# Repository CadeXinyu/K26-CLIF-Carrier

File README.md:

# K26 Closed-Loop Intan Front End — carrier board, Rev A

Carrier board for the AMD Kria K26 SOM: PCIe x4 edge connector, QSFP28 cage, FMC HPC connector,
four Intan RHD headstage ports, Gigabit Ethernet, USB, SD card and a USB JTAG/UART bridge.

## How to open the design

The easiest way to look at the board is the **KiCad** copy or the **layer PDFs** below.
The original design was made in **EasyEDA Pro** (Chinese name: 嘉立创EDA专业版), version 4.1.97.

### EasyEDA Pro (original, schematic + PCB)

File: **`design/easyeda/K26_CLIF_RevA.epro2`**

- The file was made with the 4.1 release line of the editor. Use version 4.1.97 or newer.
- Web editor with version 4.1: <https://pro.lceda.cn/editor> (the China site; it needs a free account on that site, and the interface language can be set to English).
- Desktop version: <https://lceda.cn/page/download>.
- Open it with **File → Import → EasyEDA (Professional)** and select the `.epro2` file.
- The international site <https://pro.easyeda.com/editor> runs version 3.2 at the time of writing. Importing this file there has not been tested and may fail.

This file is the reference. It contains the schematic (12 pages), the 6-layer PCB, the footprints and the design rules.

### KiCad (converted copy, PCB only)

File: **`design/kicad/K26_CLIF_RevA.kicad_pro`** (open with KiCad 10 or newer)

- It contains the PCB: all six copper layers, tracks, vias, copper pours, silkscreen and the board outline.
- It does not contain the schematic.
- The complete EasyEDA design rules are not carried over. KiCad DRC results need review against the original rules; successful import does not establish manufacturing compliance. Use this copy for viewing and measuring.
- Do not press "Fill all zones" (key B) before migrating and checking the rules. The saved copper has been checked against the original EasyEDA fill; KiCad would refill it differently.
- The 2026-11-17 checked export restores conversion omissions in cage-ground nets, embedded thermal vias, short segments and saved copper. See [conversion details](design/kicad/README.md).

### No software

| What | Where |
|---|---|
| Every layer as PDF, one file per layer | [`docs/layers/`](docs/layers/) |
| All layers in one PDF (12 pages) | [`docs/K26_CLIF_RevA_all_layers.pdf`](docs/K26_CLIF_RevA_all_layers.pdf) |
| Schematic pages as pictures | [`schematic/`](schematic/) |
| Board pictures | [`docs/`](docs/) |
| Gerber files (open with any Gerber viewer) | [`fabrication/K26_CLIF_RevA_Gerber.zip`](fabrication/K26_CLIF_RevA_Gerber.zip) |

The layer PDFs are drawn from the Gerber files, so they show exactly what is sent to the board house.
Pages: L1 top copper, L2 ground, L3 signal, L4 power, L5 ground, L6 bottom copper, top and bottom silkscreen,
top and bottom solder mask openings, top and bottom paste. The bottom-side layers are drawn as seen from the top (not mirrored).

## Routing and power pours

The three signal layers are drawn with the copper pours removed, so only tracks, pads and vias remain.
The power layer is drawn with its rail and ground pours, one colour per net.
A vector PDF of each picture is in [`docs/routing_e/`](docs/routing_e/).
The complete layers as manufactured are in [`docs/layers/`](docs/layers/).

**L1 Top (signal), pours removed**

**L3 (inner signal), pours removed**

**L6 Bottom (signal), pours removed**, seen from the top side, not mirrored

**L4 (power), rail pours and ground pours shown.** The board-wide 3.3 V pour is hidden: 3.3 V fills all the light grey area
that is not taken by another pour. The green areas are ground: the reference under the QSFP pairs and under the PCIe pairs that run on L3 (black lines).

## Stack-up

Six layers, JLCPCB stack-up **JLC06161H-3313**, ordered as 1.6 mm (finished about 1.54 mm).

| Layer | Use | Copper |
|---|---|---|
| L1 Top | Signals and components | 1 oz |
| L2 | Ground plane | 0.5 oz |
| L3 | Inner signals | 0.5 oz |
| L4 | Power planes (12 V, 5 V, 3.3 V, 1.8 V) with ground fill | 0.5 oz |
| L5 | Ground plane | 0.5 oz |
| L6 Bottom | Signals and decoupling parts | 1 oz |

Dielectric between layers: L1–L2 prepreg 3313, 0.0994 mm; L2–L3 core, 0.55 mm; L3–L4 prepreg 2116,
0.1088 mm; L4–L5 core, 0.55 mm; L5–L6 prepreg 3313, 0.0994 mm.

L3 is much closer to L4 than to L2, so the L3 tracks use L4 as their reference plane.

## Fabrication settings used for the JLCPCB quote

- 6 layers, 1.6 mm, stack-up JLC06161H-3313
- Surface finish ENIG, 1 U"
- Vias epoxy filled and capped
- Gold fingers with 30° bevel (PCIe edge)
- Minimum track and gap 0.09 mm
- Assembly on both sides

## Folder contents

| Folder | Contents |
|---|---|
| `design/easyeda/` | EasyEDA Pro project file (original) |
| `design/kicad/` | KiCad 10 copy of the PCB |
| `fabrication/` | Gerber and drill files, BOM and pick-and-place files in JLCPCB format, polarity table, assembly drawings |
| `schematic/` | The 12 schematic pages as PNG |
| `docs/` | Layer PDFs, routing pictures without pours, board renders and the stack-up drawing |

## Notes

- The `.epro2` file is the reference. The Gerber, BOM and pick-and-place files were exported from it.
- The two SOM connectors, the FMC connector and the Intan connectors are not in the assembly BOM.
  They are fitted by hand.
- The board has not been built or tested yet.

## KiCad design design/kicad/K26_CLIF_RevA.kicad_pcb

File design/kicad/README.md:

# KiCad PCB 导出说明

本目录提供与 `../easyeda/K26_CLIF_RevA.epro2` 同版的 KiCad 10 PCB 文件与最小项目文件。源 EDA 保存时间为 2026-11-17 01:33:18，SHA256：

`f1121fc5e281b10cd991b39010013871bc10f00e706a88f5d16b4b076a84ac8c`

- [PCB文件](K26_CLIF_RevA.kicad_pcb)
- [最小项目文件](K26_CLIF_RevA.kicad_pro)
转换核验摘要见 [conversion_validation.json](conversion_validation.json)。先前转换文件已另行备份。

以同版既有 KiCad 转换件为基础，核对后只校正转换丢失：恢复10个QSFP笼地焊盘的GND网名、13段0.00027–0.0023mm极短走线、12个DC/DC封装内热过孔，并将46个铜区的已保存填充恢复为原EDA的POURED实铜轮廓。另以0.1µm容差保拓扑简化已保存铜面轮廓，2355个孔洞轮廓计数保留，使文件从98.2MB降至33.7MB。没有修改原EDA，也没有调用KiCad重新铺铜。原转换件按原字节备份。

重新打开文件后验证：323个命名元件（另66个独立焊盘包装为无名封装），2240个焊盘，6898段直线、19段圆弧、1586个过孔；位置/角度、焊盘网名/尺寸/钻孔及走线几何均对应源。坐标整体平移(+50,+70)mm，板内相对位置不变；焊盘最大坐标差0.373µm，走线/圆弧/过孔按1µm容差核对。30组网络/铜层的保存实铜联合面积最大相对差约0.00330%，2µm容差外未发现面积差。

这是 **PCB-only** 导出；没有配套KiCad原理图，规则、板厂叠层参数、3D模型及完整文档未全部迁移或签核。当前保存的铜面已核对；若在KiCad中重新铺铜，应先核对并迁移设计规则。源设计中已报告的问题也被忠实保留，不能以文件成功打开替代制造检查。

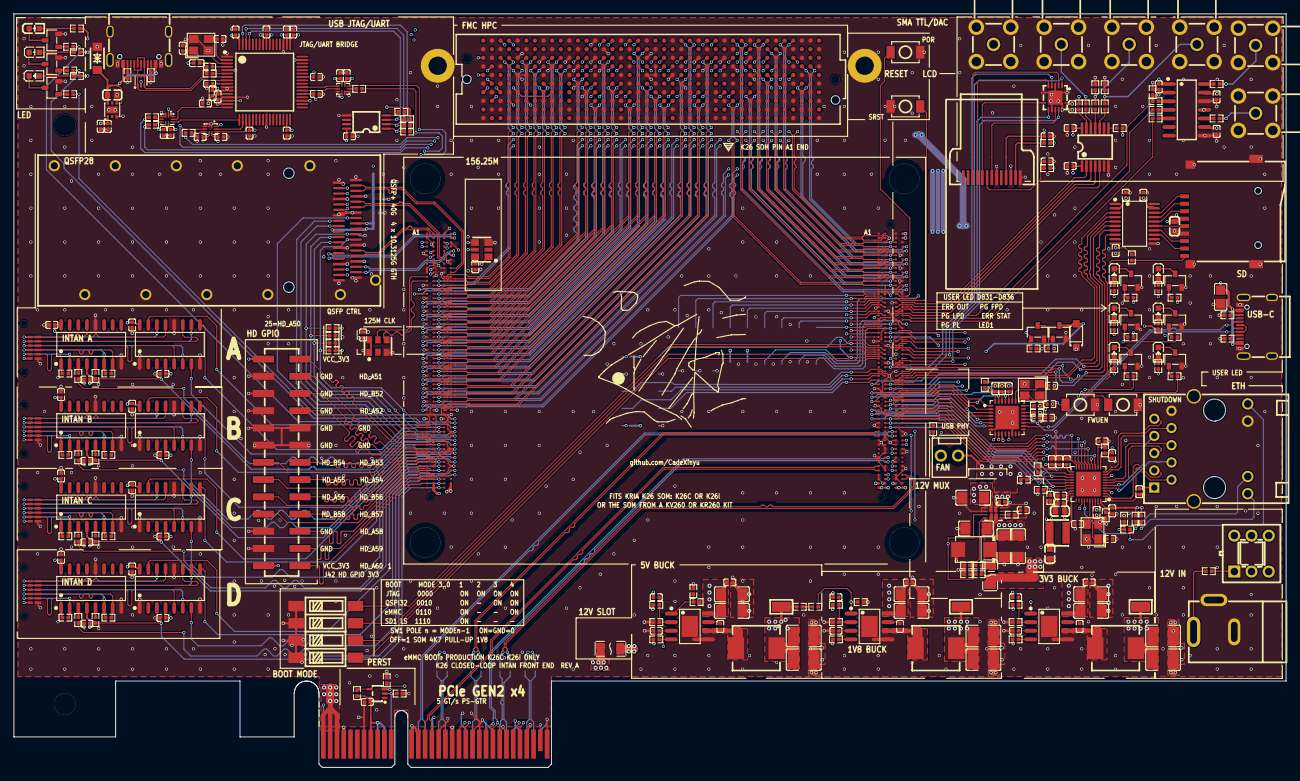
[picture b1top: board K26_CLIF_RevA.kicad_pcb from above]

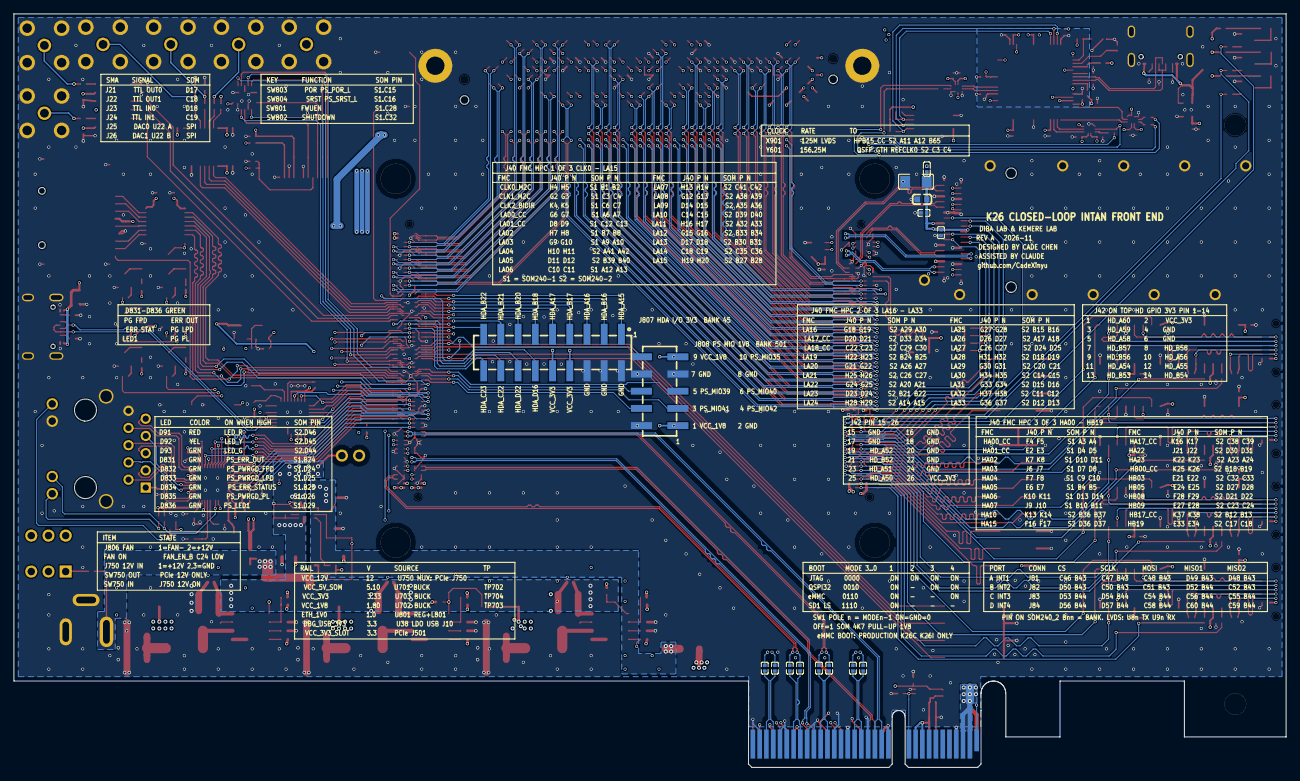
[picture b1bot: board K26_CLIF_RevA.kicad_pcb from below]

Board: 6 copper layers, 187.7 x 111.2 mm, 319 parts (15 on the bottom side), 462 nets.

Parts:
C21, C22, C23, C24, C150, C154, C156, C159, C161, C162, C163, C164, C165, C166, C167, C168, C169, C170, C171, C172, C173, C174, C175, C176, C177, C178, C502, C503, C504, C505, C506, C507, C508, C509, C513, C601, C610, C612, C712, C713, C716, C717, C722, C723, C726, C727, C732, C733, C736, C737, C752, C801, C802, C803, C806, C807, C808, C809, C810, C811, C812, C821, C822, C823, C831, C832, C841, C842, C851, C852, C853, C861, C862, C863, C864, C865, C866, C867, C881, C882, C891, C892, C893, C901, C902, C903, C904, C905, C906, C907, C908, C909, C910, C911, C912, C913: C0402
C155, C611, C804, C805, C883: C0603
C613, C700, C701, C710, C711, C720, C721, C730, C731, C750, C751: C1206
C714, C715, C724, C725, C734, C735: C1210
C868: C0805
D26: SOD-123FL_L2.8-W1.8-LS3.7-BI
D91: LED-SMD_L1.6-W0.8-R-RD
D92: LED0603-R-RD
D93, D831, D832, D833, D834, D835, D836: LED0603-RD
D750: SMB_L4.6-W3.6-LS5.3-RD
D841: SOD-123F_L2.7-W1.6-LS3.8-RD
F750, F751: F1206
FB4, FB5, FB601: L0402
J10, J803: TYPE-C-SMD_SBC-160S1A-20-S412
J21, J22, J23, J24, J25, J26: SMA-TH_KH-SMA-KWE11
J40: CONN-SMD_400P-P1.27-R10-C40
J42: HDR-SMD_26P-P2.54-V-M-R2-C13-LS7.5
J501: J501 — PCIe x4 edge
J602: CONN-SMD_QSFP2849003-00N011
J750: DC-IN-TH_PJ-002AH
J801: RJ45-TH_HR911130A
J805: TF-SMD_TF-01A
J806: CONN-TH_2P-X2510WV-02-N0SN
J807: HDR-SMD_18P-P2.54-V-M-R2-C9-S7.50-1
J808: HDR-SMD_10P-P2.54-V-M-R2-C5-LS7.5
JP701: R0402
K26: K26 — Kria K26 • 180°
L701, L702, L703: IND-SMD_L7.0-W6.6
L801: IND-SMD_L3.0-W3.0
LCD1: OLED-SMD_ST7735S
Q91, Q92, Q93, Q831, Q832, Q833, Q834, Q835, Q836, Q841, Q842: SOT-23-3_L2.9-W1.3-P1.90-LS2.4-BR
R21, R22, R23, R24, R25, R26, R27, R31, R32, R33, R34, R35, R36, R91, R92, R93, R94, R95, R96, R102, R106, R107, R108, R110, R121, R122, R123, R124, R513, R514, R515, R601, R602, R603, R604, R710, R711, R712, R713, R714, R720, R721, R722, R730, R731, R732, R740, R741, R750, R751, R752, R753, R754, R755, R801, R802, R803, R804, R805, R806, R808, R809, R810, R811, R812, R813, R814, R821, R822, R823, R824, R831, R832, R833, R834, R841, R842, R843, R844, R851, R852, R861, R862, R863, R865, R866, R891, R901, R902, R931, R932, R933, R934, R935, R936, R941, R942, R943, R944, R945, R946, R951, R952, R954, R955: R0402
SOM240_1: SOM240_1 — Samtec ADM6 4×60
SOM240_2: SOM240_2 — Samtec ADM6 4×60
SW1: SW-SMD_DSIC04LSGET
SW750: SW-TH_6P-L8.5-W8.5-P2.50-S5.30_PB-22E86
SW801, SW802, SW803, SW804: SW-SMD_L3.9-W3.0-P4.45
TP702, TP703, TP704: SMD_RH-5015
U21: TSSOP-14_L5.0-W4.4-P0.65-LS6.4-BL
U22: SOIC-14_L8.7-W3.9-P1.27-LS6.0-BL
U38: WDFN-6_L2.0-W2.0-P0.65-BL-EP-1
U39: TSSOP-8_L4.4-W3.0-P0.65-LS6.4-BL
U40: LQFP-64_L10.0-W10.0-P0.50-LS12.0-TL
U42, U43, U45: WQFN-10_L1.8-W1.4-P0.40-BL
U60: SOT-563_L1.6-W1.2-P0.50-LS1.6-BL
U81, U82, U83, U84, U91, U92, U93, U94: SOP-16_L10.0-W3.9-P1.27-LS6.0-BL
U511: SC-70-5_L2.1-W1.3-P0.65-LS2.1-BR
U701, U702, U703: SOIC-8_L4.9-W3.9-P1.27-LS6.0-BL-EP
U750: VQFN-HR-12_L2.5-W2.0-P0.50-BL
U801: WQFN-40_L5.0-W5.0-P0.4-BL-EP
U802: QFN-32_L5.0-W5.0-P0.50-BL-EP3.4
U806: TSSOP-20_L6.5-W4.4-P0.65-LS6.4-BL
U807: VQFN-14_L3.5-W3.5-P0.50-BL-EP
X901: OSC-SMD_6P-L3.2-W2.5-BL_SG3225EAN
Y7, Y801, Y802: CRYSTAL-SMD_4P-L3.2-W2.5-BL
Y601: OSC-SMD_6P-L3.2-W2.5-BL

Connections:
BST_1V8: C723.2, U702.7
BST_3V3: C733.2, U703.7
BST_5V: C713.2, U701.7
DACJ_0: J25.5, R31.2
DACJ_1: J26.5, R32.2
DAC_CS_R: R33.2, U22.3
DAC_SCK_R: R34.2, U22.4
DAC_SCLK: R34.1, SOM240_1.D20
DAC_SDIN: R35.1, SOM240_1.D21
DAC_SDI_R: R35.2, U22.5
DAC_SYNC: R33.1, R36.1, SOM240_1.C20
DAC_VOUTA: R31.1, U22.14
DAC_VOUTB: R32.1, U22.10
DBG_EECLK: R108.1, U39.2, U40.62
DBG_EECS: R110.1, U39.1, U40.63
DBG_EEDATA: R106.1, R107.2, U39.3, U40.61
DBG_EEPROM_DO: R107.1, U39.4
DBG_FTDI_REF: R102.1, U40.6
DBG_FTDI_RXD: U40.39, U45.8
DBG_FTDI_TCK: U40.16, U42.9
DBG_FTDI_TDI: U40.17, U42.8
DBG_FTDI_TDO: U40.18, U43.9
DBG_FTDI_TMS: U40.19, U43.8
DBG_FTDI_TXD: U40.38, U45.9
DBG_K26_PS_POR_N: SOM240_1.C15, SW803.1
DBG_K26_PS_SRST_N: SOM240_1.C16, SW804.2
DBG_K26_TCK: R121.2, SOM240_1.A25
DBG_K26_TDI: R122.2, SOM240_1.A24
DBG_K26_TDO: SOM240_1.A23, U43.4
DBG_K26_TMS: R123.2, SOM240_1.A22
DBG_K26_UART_RX: R124.2, SOM240_1.B30
DBG_K26_UART_TX: SOM240_1.B29, U45.5
DBG_TCK_R: R121.1, U42.4
DBG_TDI_R: R122.1, U42.5
DBG_TMS_R: R123.1, U43.5
DBG_UART_RX_R: R124.1, U45.4
DBG_USB_3V3: C150.2, C159.1, C164.1, C165.1, C167.1, C169.1, C170.1, C171.1, C173.1, C175.1, C178.1, C909.2, FB4.1, FB5.1, R106.2, R108.2, R110.2, U38.1, U39.8, U40.14, U40.20, U40.31, U40.42, U40.50, U40.56, U42.1, U42.7, U42.10, U43.7, U43.10, U45.1, U45.7
DBG_USB_CC1: J10.A5, R901.1
DBG_USB_CC2: J10.B5, R902.1
DBG_USB_N: J10.A7, J10.B7, U40.7, U60.3, U60.4
DBG_USB_P: J10.A6, J10.B6, U40.8, U60.1, U60.6
DBG_USB_VBUS: C155.1, D26.1, J10.A4, J10.A9, J10.B4, J10.B9, U38.4, U38.6
DBG_VCORE: C163.1, C166.1, C168.1, C177.1, U40.12, U40.37, U40.49, U40.64
DBG_VPHY: C161.1, FB4.2, U40.4
DBG_VPLL: C162.1, FB5.2, U40.9
DBG_XIN: C154.1, U40.2, Y7.3
DBG_XOUT: C156.1, U40.3, Y7.1
EN_5V: R713.1, R714.1, U701.1
ETH_1V0: C803.2, C804.2, C808.1, C823.1, C853.1, L801.2, U801.3, U801.8, U801.21, U801.38
ETH_CT: C852.2, J801.P1
ETH_LED1: R808.2, R809.1, U801.33
ETH_LED1_A: J801.14, R809.2
ETH_LED2: J801.12, R810.2, U801.34
ETH_LED2_A: J801.11, R851.2
ETH_MDC: SOM240_1.D44, U801.13
ETH_MDI0_N: J801.P3, U801.2
ETH_MDI0_P: J801.P2, U801.1
ETH_MDI1_N: J801.P7, U801.5
ETH_MDI1_P: J801.P4, U801.4
ETH_MDI2_N: J801.P6, U801.7
ETH_MDI2_P: J801.P5, U801.6
ETH_MDI3_N: J801.P9, U801.10
ETH_MDI3_P: J801.P8, U801.9
ETH_MDIO: R802.2, SOM240_1.D45, U801.14
ETH_REGOUT: L801.1, U801.30
ETH_RSET: R801.2, U801.39
ETH_RSTB: C809.1, R803.1, U801.12
ETH_RXC: R806.2, SOM240_1.B44, U801.27
ETH_RXCTL: R805.2, SOM240_1.A44, U801.26
ETH_RXD0: SOM240_1.B45, U801.25
ETH_RXD1: R852.2, SOM240_1.B46, U801.24
ETH_RXD2: R804.2, SOM240_1.A42, U801.23
ETH_RXD3: SOM240_1.A43, U801.22
ETH_TXC: SOM240_1.D40, U801.20
ETH_TXCTL: SOM240_1.C44, U801.19
ETH_TXD0: SOM240_1.D41, U801.18
ETH_TXD1: SOM240_1.D42, U801.17
ETH_TXD2: SOM240_1.C42, U801.16
ETH_TXD3: SOM240_1.C43, U801.15
ETH_VDDRG: C807.2, U801.28
ETH_XI: C810.2, U801.36, Y801.3
ETH_XO: C851.1, U801.37, Y801.1
FAN_EN_B: Q841.1, R951.1, SOM240_1.C24
FAN_G: Q841.3, Q842.1, R952.1
FAN_N: D841.2, J806.1, Q842.3
FB_1V8: C727.2, R720.2, R721.2, U702.2
FB_3V3: C737.2, R730.2, R731.2, U703.2
FB_5V: C717.2, R710.2, R711.2, U701.2
GND: C21.1, C22.1, C23.1, C24.2, C150.1, C154.2, C155.2, C156.2, C159.2, C161.2, C162.2, C163.2, C164.2, C165.2, C166.2, C167.2, C168.2, C169.2, C170.2, C171.2, C172.2, C173.2, C174.2, C175.2, C176.2, C177.2, C178.2, C513.2, C601.1, C610.2, C611.2, C612.1, C613.2, C700.2, C701.2, C710.2, C711.2, C712.2, C714.2, C715.2, C716.1, C720.2, C721.2, C722.2, C724.2, C725.2, C726.1, C730.2, C731.2, C732.2, C734.2, C735.2, C736.1, C750.2, C751.2, C752.1, C801.1, C802.1, C803.1, C804.1, C805.1, C806.1, C807.1, C808.2, C809.2, C810.1, C811.1, C812.1, C821.2, C822.1, C823.2, C831.2, C832.1, C841.2, C842.1, C851.2, C852.1, C853.2, C861.2, C862.1, C863.2, C864.2, C865.1, C866.1, C867.1, C868.1, C881.2, C882.2, C883.1, C891.2, C892.2, C893.2, C901.2, C902.1, C903.2, C904.1, C905.2, C906.2, C907.2, C908.2, C909.1, C910.1, C911.1, C912.1, C913.1, D26.2, D750.2, J10.1, J10.2, J10.3, J10.4, J10.A1, J10.A12, J10.B1, J10.B12, J21.1, J21.2, J21.3, J21.4, J22.1, J22.2, J22.3, J22.4, J23.1, J23.2, J23.3, J23.4, J24.1, J24.2, J24.3, J24.4, J25.1, J25.2, J25.3, J25.4, J26.1, J26.2, J26.3, J26.4, J40.A1, J40.A4, J40.A5, J40.A8, J40.A9, J40.A12, J40.A13, J40.A16, J40.A17, J40.A20, J40.A21, J40.A24, J40.A25, J40.A28, J40.A29, J40.A32, J40.A33, J40.A36, J40.A37, J40.A40, J40.B2, J40.B3, J40.B6, J40.B7, J40.B10, J40.B11, J40.B14, J40.B15, J40.B18, J40.B19, J40.B22, J40.B23, J40.B26, J40.B27, J40.B30, J40.B31, J40.B34, J40.B35, J40.B38, J40.B39, J40.C1, J40.C4, J40.C5, J40.C8, J40.C9, J40.C12, J40.C13, J40.C16, J40.C17, J40.C20, J40.C21, J40.C24, J40.C25, J40.C28, J40.C29, J40.C32, J40.C33, J40.C36, J40.C38, J40.C40, J40.D2, J40.D3, J40.D6, J40.D7, J40.D10, J40.D13, J40.D16, J40.D19, J40.D22, J40.D25, J40.D28, J40.D37, J40.D39, J40.E1, J40.E4, J40.E5, J40.E8, J40.E11, J40.E14, J40.E17, J40.E20, J40.E23, J40.E26, J40.E29, J40.E32, J40.E35, J40.E38, J40.E40, J40.F2, J40.F3, J40.F6, J40.F9, J40.F12, J40.F15, J40.F18, J40.F20, J40.F21, J40.F24, J40.F27, J40.F30, J40.F33, J40.F35, J40.F36, J40.F39, J40.G1, J40.G4, J40.G5, J40.G8, J40.G11, J40.G14, J40.G17, J40.G20, J40.G23, J40.G26, J40.G29, J40.G32, J40.G35, J40.G38, J40.G40, J40.H3, J40.H6, J40.H9, J40.H12, J40.H15, J40.H18, J40.H21, J40.H24, J40.H27, J40.H30, J40.H33, J40.H36, J40.H39, J40.J1, J40.J4, J40.J5, J40.J8, J40.J11, J40.J14, J40.J17, J40.J20, J40.J23, J40.J26, J40.J29, J40.J32, J40.J35, J40.J38, J40.J40, J40.K2, J40.K3, J40.K6, J40.K9, J40.K12, J40.K15, J40.K18, J40.K21, J40.K24, J40.K27, J40.K30, J40.K33, J40.K36, J40.K39, J42.4, J42.6, J42.15, J42.16, J42.17, J42.18, J42.20, J42.22, J42.24, J501.A4, J501.A12, J501.A15, J501.A18, J501.A20, J501.A23, J501.A24, J501.A27, J501.A28, J501.A31, J501.B4, J501.B7, J501.B13, J501.B16, J501.B18, J501.B21, J501.B22, J501.B25, J501.B26, J501.B29, J501.B32, J602.1, J602.4, J602.7, J602.13, J602.16, J602.19, J602.20, J602.23, J602.26, J602.32, J602.35, J602.38, J602.39, J750.2, J750.3, J801.13, J801.P10, J801.SHIELD0, J801.SHIELD1, J803.1, J803.2, J803.3, J803.4, J803.A1, J803.A12, J803.B1, J803.B12, J805.6, J805.10, J805.11, J805.12, J805.13, J807.2, J807.4, J807.6, J808.2, J808.7, J808.8, LCD1.8, LCD1.11, LCD1.13, Q91.2, Q92.2, Q93.2, Q831.2, Q832.2, Q833.2, Q834.2, Q835.2, Q836.2, Q841.2, Q842.2, R25.1, R26.1, R102.2, R513.1, R515.2, R710.1, R714.2, R720.1, R730.1, R740.2, R751.1, R753.2, R754.1, R801.1, R804.1, R805.1, R806.1, R808.1, R861.2, R865.1, R866.1, R901.2, R902.2, R951.2, SOM240_1.A1, SOM240_1.A2, SOM240_1.A5, SOM240_1.A8, SOM240_1.A11, SOM240_1.A14, SOM240_1.A18, SOM240_1.A21, SOM240_1.A26, SOM240_1.A33, SOM240_1.A37, SOM240_1.A41, SOM240_1.A45, SOM240_1.A46, SOM240_1.A49, SOM240_1.A50, SOM240_1.A53, SOM240_1.A54, SOM240_1.A57, SOM240_1.A58, SOM240_1.B3, SOM240_1.B6, SOM240_1.B9, SOM240_1.B12, SOM240_1.B15, SOM240_1.B19, SOM240_1.B23, SOM240_1.B27, SOM240_1.B31, SOM240_1.B35, SOM240_1.B39, SOM240_1.B43, SOM240_1.B47, SOM240_1.B48, SOM240_1.B51, SOM240_1.B52, SOM240_1.B55, SOM240_1.B56, SOM240_1.B59, SOM240_1.C1, SOM240_1.C2, SOM240_1.C5, SOM240_1.C8, SOM240_1.C11, SOM240_1.C14, SOM240_1.C17, SOM240_1.C21, SOM240_1.C25, SOM240_1.C29, SOM240_1.C33, SOM240_1.C37, SOM240_1.C41, SOM240_1.C46, SOM240_1.C49, SOM240_1.C50, SOM240_1.C53, SOM240_1.C54, SOM240_1.C57, SOM240_1.C58, SOM240_1.D3, SOM240_1.D6, SOM240_1.D9, SOM240_1.D12, SOM240_1.D15, SOM240_1.D19, SOM240_1.D23, SOM240_1.D27, SOM240_1.D31, SOM240_1.D35, SOM240_1.D39, SOM240_1.D43, SOM240_1.D47, SOM240_1.D48, SOM240_1.D51, SOM240_1.D52, SOM240_1.D55, SOM240_1.D56, SOM240_1.D59, SOM240_2.A1, SOM240_2.A2, SOM240_2.A5, SOM240_2.A6, SOM240_2.A9, SOM240_2.A10, SOM240_2.A13, SOM240_2.A16, SOM240_2.A19, SOM240_2.A22, SOM240_2.A25, SOM240_2.A28, SOM240_2.A31, SOM240_2.A34, SOM240_2.A37, SOM240_2.A40, SOM240_2.A43, SOM240_2.A45, SOM240_2.A49, SOM240_2.A53, SOM240_2.A57, SOM240_2.B3, SOM240_2.B4, SOM240_2.B7, SOM240_2.B8, SOM240_2.B11, SOM240_2.B14, SOM240_2.B17, SOM240_2.B20, SOM240_2.B23, SOM240_2.B26, SOM240_2.B29, SOM240_2.B32, SOM240_2.B35, SOM240_2.B38, SOM240_2.B41, SOM240_2.B43, SOM240_2.B47, SOM240_2.B51, SOM240_2.B55, SOM240_2.C1, SOM240_2.C2, SOM240_2.C5, SOM240_2.C6, SOM240_2.C9, SOM240_2.C10, SOM240_2.C13, SOM240_2.C16, SOM240_2.C19, SOM240_2.C22, SOM240_2.C25, SOM240_2.C28, SOM240_2.C31, SOM240_2.C34, SOM240_2.C37, SOM240_2.C40, SOM240_2.C43, SOM240_2.C45, SOM240_2.C49, SOM240_2.C53, SOM240_2.C57, SOM240_2.D3, SOM240_2.D4, SOM240_2.D7, SOM240_2.D8, SOM240_2.D11, SOM240_2.D14, SOM240_2.D17, SOM240_2.D20, SOM240_2.D23, SOM240_2.D26, SOM240_2.D29, SOM240_2.D32, SOM240_2.D35, SOM240_2.D38, SOM240_2.D41, SOM240_2.D43, SOM240_2.D47, SOM240_2.D51, SOM240_2.D55, SW1.1, SW1.2, SW1.3, SW1.4, SW801.2, SW802.2, SW803.2, SW804.1, U21.7, U22.8, U22.12, U38.3, U38.7, U39.5, U40.1, U40.5, U40.10, U40.11, U40.13, U40.15, U40.25, U40.35, U40.47, U40.51, U42.2, U42.3, U43.1, U43.2, U43.3, U45.2, U45.3, U45.10, U60.2, U81.1, U81.8, U81.12, U82.1, U82.8, U82.12, U83.1, U83.8, U83.12, U84.1, U84.8, U84.12, U91.8, U91.12, U92.8, U92.12, U93.8, U93.12, U94.8, U94.12, U511.3, U701.5, U701.9, U702.5, U702.9, U703.5, U703.9, U750.3, U750.4, U750.9, U750.12, U801.41, U802.8, U802.14, U802.33, U806.11, U807.1, U807.4, U807.7, U807.10, U807.13, U807.15, X901.3, Y7.2, Y7.4, Y601.3, Y801.2, Y801.4, Y802.2, Y802.4
HDA_A15: J807.1, SOM240_1.A15
HDA_A16: J807.5, SOM240_1.A16
HDA_A17: J807.9, SOM240_1.A17
HDA_B16: J807.3, SOM240_1.B16
HDA_B17: J807.7, SOM240_1.B17
HDA_B18: J807.11, SOM240_1.B18
HDA_B20: J807.13, SOM240_1.B20
HDA_B21: J807.15, SOM240_1.B21
HDA_B22: J807.17, SOM240_1.B22
HDA_C22: J807.16, SOM240_1.C22
HDA_C23: J807.18, SOM240_1.C23
HDA_D16: J807.12, SOM240_1.D16
HDA_D22: J807.14, SOM240_1.D22
HD_A50: J42.25, SOM240_2.A50
HD_A51: J42.23, SOM240_2.A51
HD_A52: J42.19, SOM240_2.A52
HD_A54: J42.11, SOM240_2.A54
HD_A55: J42.12, SOM240_2.A55
HD_A56: J42.10, SOM240_2.A56
HD_A58: J42.5, SOM240_2.A58
HD_A59: J42.3, SOM240_2.A59
HD_A60: J42.1, SOM240_2.A60
HD_B52: J42.21, SOM240_2.B52
HD_B53: J42.13, SOM240_2.B53
HD_B54: J42.14, SOM240_2.B54
HD_B56: J42.9, SOM240_2.B56
HD_B57: J42.7, SOM240_2.B57
HD_B58: J42.8, SOM240_2.B58
HPA00_CC_N: J40.G3, SOM240_1.C4
HPA00_CC_P: J40.G2, SOM240_1.C3
HPA01_N: J40.J7, SOM240_1.D8
HPA01_P: J40.J6, SOM240_1.D7
HPA02_N: J40.E3, SOM240_1.D5
HPA02_P: J40.E2, SOM240_1.D4
HPA03_N: J40.K5, SOM240_1.C7
HPA03_P: J40.K4, SOM240_1.C6
HPA04_N: J40.E7, SOM240_1.B5
HPA04_P: J40.E6, SOM240_1.B4
HPA05_CC_N: J40.H5, SOM240_1.B2
HPA05_CC_P: J40.H4, SOM240_1.B1
HPA06_N: J40.F5, SOM240_1.A4
HPA06_P: J40.F4, SOM240_1.A3
HPA07_N: J40.H8, SOM240_1.B8
HPA07_P: J40.H7, SOM240_1.B7
HPA08_N: J40.F8, SOM240_1.C10
HPA08_P: J40.F7, SOM240_1.C9
HPA09_N: J40.K8, SOM240_1.D11
HPA09_P: J40.K7, SOM240_1.D10
HPA10_CC_N: J40.D9, SOM240_1.C13
HPA10_CC_P: J40.D8, SOM240_1.C12
HPA11_N: J40.J10, SOM240_1.B11
HPA11_P: J40.J9, SOM240_1.B10
HPA12_N: J40.G10, SOM240_1.A10
HPA12_P: J40.G9, SOM240_1.A9
HPA13_N: J40.C11, SOM240_1.A13
HPA13_P: J40.C10, SOM240_1.A12
HPA14_N: J40.K11, SOM240_1.D14
HPA14_P: J40.K10, SOM240_1.D13
HPA_CLK0_N: J40.G7, SOM240_1.A7
HPA_CLK0_P: J40.G6, SOM240_1.A6
HPB00_CC_N: J40.G34, SOM240_2.D16
HPB00_CC_P: J40.G33, SOM240_2.D15
HPB01_N: J40.G37, SOM240_2.D13
HPB01_P: J40.G36, SOM240_2.D12
HPB02_N: J40.E34, SOM240_2.C18
HPB02_P: J40.E33, SOM240_2.C17
HPB03_N: J40.H23, SOM240_2.B25
HPB03_P: J40.H22, SOM240_2.B24
HPB04_N: J40.F29, SOM240_2.D22
HPB04_P: J40.F28, SOM240_2.D21
HPB05_CC_N: J40.K26, SOM240_2.B19
HPB05_CC_P: J40.K25, SOM240_2.B18
HPB06_N: J40.G25, SOM240_2.A21
HPB06_P: J40.G24, SOM240_2.A20
HPB07_N: J40.G28, SOM240_2.B16
HPB07_P: J40.G27, SOM240_2.B15
HPB08_N: J40.H29, SOM240_2.A15
HPB08_P: J40.H28, SOM240_2.A14
HPB09_N: J40.H38, SOM240_2.C12
HPB09_P: J40.H37, SOM240_2.C11
HPB10_CC_N: J40.K38, SOM240_2.B13
HPB10_CC_P: J40.K37, SOM240_2.B12
HPB11_N: J40.D24, SOM240_2.B22
HPB11_P: J40.D23, SOM240_2.B21
HPB12_N: J40.D27, SOM240_2.A18
HPB12_P: J40.D26, SOM240_2.A17
HPB13_N: J40.G31, SOM240_2.C21
HPB13_P: J40.G30, SOM240_2.C20
HPB14_N: J40.H35, SOM240_2.C15
HPB14_P: J40.H34, SOM240_2.C14
HPB15_CC_N: SOM240_2.A12, X901.4
HPB15_CC_P: SOM240_2.A11, X901.5
HPB16_N: J40.K23, SOM240_2.A24
HPB16_P: J40.K22, SOM240_2.A23
HPB17_N: J40.C27, SOM240_2.D25
HPB17_P: J40.C26, SOM240_2.D24
HPB_18_N: J40.E28, SOM240_2.C24
HPB_18_P: J40.E27, SOM240_2.C23
HPB_19_N: J40.G22, SOM240_2.A27
HPB_19_P: J40.G21, SOM240_2.A26
HPB_CLK0_N: J40.H32, SOM240_2.D19
HPB_CLK0_P: J40.H31, SOM240_2.D18
HPC00_CC_N: J40.D21, SOM240_2.D34
HPC00_CC_P: J40.D20, SOM240_2.D33
HPC01_N: J40.J22, SOM240_2.D31
HPC01_P: J40.J21, SOM240_2.D30
HPC02_N: J40.F17, SOM240_2.D37
HPC02_P: J40.F16, SOM240_2.D36
HPC03_N: J40.H11, SOM240_2.A42
HPC03_P: J40.H10, SOM240_2.A41
HPC04_N: J40.C15, SOM240_2.D40
HPC04_P: J40.C14, SOM240_2.D39
HPC05_CC_N: J40.K17, SOM240_2.C39
HPC05_CC_P: J40.K16, SOM240_2.C38
HPC06_N: J40.H20, SOM240_2.B28
HPC06_P: J40.H19, SOM240_2.B27
HPC07_N: J40.K14, SOM240_2.B37
HPC07_P: J40.K13, SOM240_2.B36
HPC08_N: J40.G19, SOM240_2.A30
HPC08_P: J40.G18, SOM240_2.A29
HPC09_N: J40.E25, SOM240_2.D28
HPC09_P: J40.E24, SOM240_2.D27
HPC10_CC_N: J40.C23, SOM240_2.C30
HPC10_CC_P: J40.C22, SOM240_2.C29
HPC11_N: J40.E22, SOM240_2.C33
HPC11_P: J40.E21, SOM240_2.C32
HPC12_N: J40.C19, SOM240_2.C36
HPC12_P: J40.C18, SOM240_2.C35
HPC13_N: J40.D18, SOM240_2.B31
HPC13_P: J40.D17, SOM240_2.B30
HPC14_N: J40.D15, SOM240_2.A36
HPC14_P: J40.D14, SOM240_2.A35
HPC15_CC_N: J40.G13, SOM240_2.A39
HPC15_CC_P: J40.G12, SOM240_2.A38
HPC16_N: J40.G16, SOM240_2.B34
HPC16_P: J40.G15, SOM240_2.B33
HPC17_N: J40.H26, SOM240_2.C27
HPC17_P: J40.H25, SOM240_2.C26
HPC18_N: J40.D12, SOM240_2.B40
HPC18_P: J40.D11, SOM240_2.B39
HPC19_N: J40.H17, SOM240_2.A33
HPC19_P: J40.H16, SOM240_2.A32
HPC_CLK0_N: J40.H14, SOM240_2.C42
HPC_CLK0_P: J40.H13, SOM240_2.C41
INT1_CS: SOM240_2.C46, U81.15
INT1_MISO1: R811.1, SOM240_2.D49
INT1_MISO1_N: R813.2, U91.7
INT1_MISO1_P: R813.1, U91.6
INT1_MISO1_R: R811.2, U91.5
INT1_MISO2: R812.1, SOM240_2.D48
INT1_MISO2_N: R814.1, U91.1
INT1_MISO2_P: R814.2, U91.2
INT1_MISO2_R: R812.2, U91.3
INT1_MOSI: SOM240_2.C48, U81.7
INT1_SCLK: SOM240_2.C47, U81.9
INT2_CS: SOM240_2.D50, U82.15
INT2_MISO1: R821.1, SOM240_2.D52
INT2_MISO1_N: R823.2, U92.7
INT2_MISO1_P: R823.1, U92.6
INT2_MISO1_R: R821.2, U92.5
INT2_MISO2: R822.1, SOM240_2.C52
INT2_MISO2_N: R824.1, U92.1
INT2_MISO2_P: R824.2, U92.2
INT2_MISO2_R: R822.2, U92.3
INT2_MOSI: SOM240_2.C51, U82.7
INT2_SCLK: SOM240_2.C50, U82.9
INT3_CS: SOM240_2.D53, U83.15
INT3_MISO1: R831.1, SOM240_2.C56
INT3_MISO1_N: R833.2, U93.7
INT3_MISO1_P: R833.1, U93.6
INT3_MISO1_R: R831.2, U93.5
INT3_MISO2: R832.1, SOM240_2.C55
INT3_MISO2_N: R834.1, U93.1
INT3_MISO2_P: R834.2, U93.2
INT3_MISO2_R: R832.2, U93.3
INT3_MOSI: SOM240_2.C54, U83.7
INT3_SCLK: SOM240_2.D54, U83.9
INT4_CS: SOM240_2.D56, U84.15
INT4_MISO1: R841.1, SOM240_2.C60
INT4_MISO1_N: R843.2, U94.7
INT4_MISO1_P: R843.1, U94.6
INT4_MISO1_R: R841.2, U94.5
INT4_MISO2: R842.1, SOM240_2.C59
INT4_MISO2_N: R844.1, U94.1
INT4_MISO2_P: R844.2, U94.2
INT4_MISO2_R: R842.2, U94.3
INT4_MOSI: SOM240_2.C58, U84.7
INT4_SCLK: SOM240_2.D57, U84.9
K26_MODE0: SOM240_1.A27, SW1.8
K26_MODE1: SOM240_1.A28, SW1.7
K26_MODE2: SOM240_1.A29, SW1.6
K26_MODE3: SOM240_1.A30, SW1.5
K26_VCCOEN_PL: JP701.2, R740.1, SOM240_1.A20, U702.1, U703.1
LCD_CS: LCD1.7, U807.11
LCD_DC: LCD1.5, U807.8
LCD_LEDA: LCD1.12, R954.1
LCD_RST: C892.1, LCD1.6, R955.1
LCD_SCL: LCD1.4, U807.6
LCD_SDA: LCD1.3, U807.3
LED_G: R96.2, SOM240_2.D44
LED_G_A: D93.2, R93.1
LED_G_B: Q93.1, R96.1
LED_G_K: D93.1, Q93.3
LED_R: R94.2, SOM240_2.D46
LED_R_A: D91.1, R91.1
LED_R_B: Q91.1, R94.1
LED_R_K: D91.2, Q91.3
LED_Y: R95.2, SOM240_2.D45
LED_Y_A: D92.1, R92.1
LED_Y_B: Q92.1, R95.1
LED_Y_K: D92.2, Q92.3
MUX_ILM: R754.2, U750.10
MUX_OV1: R752.2, R753.1, SW750.2, U750.5
MUX_PR1: R750.2, R751.2, U750.6
MUX_SS: C752.2, U750.11
MUX_SW: R755.2, SW750.1
PCIE_PERST_HOST_N: J501.A11, R513.2, U511.2
PCIE_PERST_N: R514.1, R515.1, SOM240_1.C30, U511.4
PCIE_PRSNT: J501.A1, J501.B31
PCIE_REFCLK_N: J501.A14, SOM240_1.C48
PCIE_REFCLK_P: J501.A13, SOM240_1.C47
PCIE_RX0_N: J501.B15, SOM240_1.A56
PCIE_RX0_P: J501.B14, SOM240_1.A55
PCIE_RX1_N: J501.B20, SOM240_1.C56
PCIE_RX1_P: J501.B19, SOM240_1.C55
PCIE_RX2_N: J501.B24, SOM240_1.B54
PCIE_RX2_P: J501.B23, SOM240_1.B53
PCIE_RX3_N: J501.B28, SOM240_1.D49
PCIE_RX3_P: J501.B27, SOM240_1.D50
PCIE_TX0_N: C503.1, SOM240_1.B58
PCIE_TX0_N_EDGE: C503.2, J501.A17
PCIE_TX0_P: C502.1, SOM240_1.B57
PCIE_TX0_P_EDGE: C502.2, J501.A16
PCIE_TX1_N: C505.1, SOM240_1.A48
PCIE_TX1_N_EDGE: C505.2, J501.A22
PCIE_TX1_P: C504.1, SOM240_1.A47
PCIE_TX1_P_EDGE: C504.2, J501.A21
PCIE_TX2_N: C507.1, SOM240_1.D57
PCIE_TX2_N_EDGE: C507.2, J501.A26
PCIE_TX2_P: C506.1, SOM240_1.D58
PCIE_TX2_P_EDGE: C506.2, J501.A25
PCIE_TX3_N: C509.1, SOM240_1.C52
PCIE_TX3_N_EDGE: C509.2, J501.A30
PCIE_TX3_P: C508.1, SOM240_1.C51
PCIE_TX3_P_EDGE: C508.2, J501.A29
PG_1V8: R722.2, U702.4
PG_3V3: R732.2, U703.4
PG_5V: R712.2, SOM240_1.B26, U701.4
PLED1_A: D831.2, R931.2
PLED1_B: Q831.1, R941.1
PLED1_K: D831.1, Q831.3
PLED2_A: D832.2, R932.2
PLED2_B: Q832.1, R942.1
PLED2_K: D832.1, Q832.3
PLED3_A: D833.2, R933.2
PLED3_B: Q833.1, R943.1
PLED3_K: D833.1, Q833.3
PLED4_A: D834.2, R934.2
PLED4_B: Q834.1, R944.1
PLED4_K: D834.1, Q834.3
PLED5_A: D835.2, R935.2
PLED5_B: Q835.1, R945.1
PLED5_K: D835.1, Q835.3
PLED6_A: D836.2, R936.2
PLED6_B: Q836.1, R946.1
PLED6_K: D836.1, Q836.3
PS_ERR_OUT: R941.2, SOM240_1.B24
PS_ERR_STATUS: R944.2, SOM240_1.B25
PS_FWUEN: SOM240_1.C28, SW801.1
PS_LCD_CS: SOM240_1.C31, U807.12
PS_LCD_DC: SOM240_1.D28, U807.9
PS_LCD_SCL: SOM240_1.B32, U807.5
PS_LCD_SDA: SOM240_1.A36, U807.2
PS_LED1: R946.2, SOM240_1.D29
PS_MIO35: J808.10, SOM240_1.B28
PS_MIO39: J808.5, SOM240_1.B33
PS_MIO40: J808.6, SOM240_1.B34
PS_MIO41: J808.3, SOM240_1.A34
PS_MIO42: J808.4, SOM240_1.A35
PS_PWRGD_FPD: R942.2, SOM240_1.D24
PS_PWRGD_LPD: R943.2, SOM240_1.D25
PS_PWRGD_PL: R945.2, SOM240_1.D26
PS_SHUTDOWN: SOM240_1.C32, SW802.1
PWR_TEST_EN: JP701.1, R741.2
QSFP_INT_L: J602.28, R601.1, SOM240_2.B48
QSFP_LPMODE: J602.31, SOM240_2.B50
QSFP_MODPRS_L: J602.27, R602.1, SOM240_2.B46
QSFP_MODSEL_L: J602.8, SOM240_2.B49
QSFP_REFCLK_N: SOM240_2.C4, Y601.5
QSFP_REFCLK_P: SOM240_2.C3, Y601.4
QSFP_RESET_L: J602.9, SOM240_2.A48
QSFP_RX0_N: J602.18, SOM240_2.B10
QSFP_RX0_P: J602.17, SOM240_2.B9
QSFP_RX1_N: J602.21, SOM240_2.D6
QSFP_RX1_P: J602.22, SOM240_2.D5
QSFP_RX2_N: J602.15, SOM240_2.D2
QSFP_RX2_P: J602.14, SOM240_2.D1
QSFP_RX3_N: J602.24, SOM240_2.B2
QSFP_RX3_P: J602.25, SOM240_2.B1
QSFP_SCL: J602.11, R603.1, SOM240_2.A47
QSFP_SDA: J602.12, R604.1, SOM240_2.A46
QSFP_TX0_N: J602.37, SOM240_2.D10
QSFP_TX0_P: J602.36, SOM240_2.D9
QSFP_TX1_N: J602.2, SOM240_2.A3
QSFP_TX1_P: J602.3, SOM240_2.A4
QSFP_TX2_N: J602.34, SOM240_2.C7
QSFP_TX2_P: J602.33, SOM240_2.C8
QSFP_TX3_N: J602.5, SOM240_2.B6
QSFP_TX3_P: J602.6, SOM240_2.B5
SDC_CLK: J805.5, U806.15
SDC_CMD: J805.3, U806.16
SDC_D0: J805.7, U806.14
SDC_D1: J805.8, U806.13
SDC_D2: J805.1, U806.18
SDC_D3: J805.2, U806.17
SD_CD: J805.9, R891.1, SOM240_1.D33
SD_CLK: SOM240_1.B37, U806.6
SD_CMD: SOM240_1.B36, U806.5
SD_D0: SOM240_1.D34, U806.7
SD_D1: SOM240_1.C34, U806.8
SD_D2: SOM240_1.C35, U806.3
SD_D3: SOM240_1.C36, U806.4
SW_1V8: C723.1, L702.1, U702.6
SW_3V3: C733.1, L703.1, U703.6
SW_5V: C713.1, L701.1, U701.6
TTLB_IN0: R22.1, U21.11
TTLB_IN1: R21.1, U21.10
TTLB_OUT0: R24.1, U21.13
TTLB_OUT1: R23.1, U21.12
TTLJ_IN0: J23.5, R22.2, R25.2
TTLJ_IN1: J24.5, R21.2, R26.2
TTLJ_OUT0: J21.5, R24.2
TTLJ_OUT1: J22.5, R23.2
TTL_IN_0: SOM240_1.D18, U21.4
TTL_IN_1: SOM240_1.C19, U21.5
TTL_OE: R27.1, U21.8
TTL_OUT_0: SOM240_1.D17, U21.2
TTL_OUT_1: SOM240_1.C18, U21.3
USB_CC1: J803.A5, R865.2
USB_CC2: J803.B5, R866.2
USB_CLK: SOM240_1.D36, U802.1
USB_D0: SOM240_1.C39, U802.3
USB_D1: SOM240_1.C40, U802.4
USB_D2: SOM240_1.D38, U802.5
USB_D3: SOM240_1.B41, U802.6
USB_D4: SOM240_1.B42, U802.7
USB_D5: SOM240_1.A38, U802.9
USB_D6: SOM240_1.A39, U802.10
USB_D7: SOM240_1.A40, U802.13
USB_DIR: SOM240_1.D37, U802.31
USB_DM: J803.A7, J803.B7, U802.19
USB_DP: J803.A6, J803.B6, U802.18
USB_NXT: SOM240_1.C38, U802.2
USB_RBIAS: R861.1, U802.24
USB_RSTB: R863.1, U802.27
USB_STP: SOM240_1.B40, U802.29
USB_VBUS: C868.2, J803.A4, J803.A9, J803.B4, J803.B9, R862.2
USB_VBUSP: R862.1, U802.22
USB_XI: C862.2, U802.26, Y802.1
USB_XO: C861.1, U802.25, Y802.3
VCC_1V8: C172.1, C174.1, C176.1, C724.1, C725.1, C727.1, C865.2, C866.2, C867.2, C881.1, C904.2, J40.E39, J40.F40, J40.G39, J40.H40, J808.1, J808.9, L702.2, R721.1, R722.1, R802.1, R852.1, R863.2, R891.2, SOM240_1.D1, SOM240_1.D2, SOM240_2.A44, SOM240_2.B42, SOM240_2.C44, SOM240_2.D42, TP703.1, U42.6, U43.6, U45.6, U802.11, U802.28, U802.30, U802.32, U806.2, U806.10
VCC_3V3: C21.2, C22.2, C23.2, C24.1, C601.2, C734.1, C735.1, C737.1, C801.2, C802.2, C805.2, C806.2, C811.2, C812.2, C821.1, C822.2, C831.1, C832.2, C841.1, C842.2, C863.1, C864.1, C882.1, C883.2, C891.1, C893.1, C901.1, C902.2, C905.1, C906.1, C907.1, C908.1, C910.2, C911.2, C912.2, C913.2, FB601.2, J40.C39, J40.D32, J40.D36, J40.D38, J40.D40, J42.2, J42.26, J805.4, J807.8, J807.10, L703.2, LCD1.10, R27.2, R36.2, R91.2, R92.2, R93.2, R601.2, R602.2, R603.2, R604.2, R731.1, R732.1, R803.2, R810.1, R851.1, R931.1, R932.1, R933.1, R934.1, R935.1, R936.1, R952.2, R954.2, R955.2, SOM240_1.B13, SOM240_1.B14, SOM240_2.B59, SOM240_2.B60, SOM240_2.D59, SOM240_2.D60, TP704.1, U21.1, U21.14, U22.1, U22.9, U22.11, U22.13, U81.4, U81.16, U82.4, U82.16, U83.4, U83.16, U84.4, U84.16, U91.4, U91.16, U92.4, U92.16, U93.4, U93.16, U94.4, U94.16, U801.11, U801.29, U801.40, U802.20, U802.21, U806.19, U807.14, X901.1, X901.6, Y601.1, Y601.6
VCC_3V3_QSFP: C610.1, C611.1, C612.2, C613.1, FB601.1, J602.10, J602.29, J602.30
VCC_3V3_SLOT: C513.1, J501.A9, J501.A10, J501.B8, R514.2, U511.5
VCC_5V_SOM: C714.1, C715.1, C717.1, L701.2, R711.1, R712.1, R741.1, SOM240_1.A59, SOM240_1.A60, SOM240_1.B60, SOM240_1.C59, SOM240_1.C60, SOM240_1.D60, TP702.1
VCC_12V: C700.1, C701.1, C710.1, C711.1, C712.1, C720.1, C721.1, C722.1, C730.1, C731.1, C732.1, C903.1, D841.1, J40.C35, J40.C37, J806.2, R713.2, U701.8, U702.8, U703.8, U750.1, U750.8
VCC_12V_AUX: C750.1, D750.1, F750.1, R750.1, R752.1, U750.7
VCC_12V_AUX_IN: F750.2, J750.1, R755.1
VCC_12V_SLOT: F751.1, J501.A2, J501.A3, J501.B1, J501.B2, J501.B3
VCC_12V_SLOT_F: C751.1, F751.2, U750.2
VREG5_1V8: C726.2, U702.3
VREG5_3V3: C736.2, U703.3
VREG5_5V: C716.2, U701.3

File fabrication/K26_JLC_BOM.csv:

Comment,Designator,Footprint,LCSC Part #
CL05B104KO5NNNC,"C21,C22,C23,C24,C161,C162,C163,C164,C165,C166,C167,C169,C170,C171,C172,C173,C174,C175,C176,C177,C178,C502,C503,C504,C505,C506,C507,C508,C509,C513,C601,C610,C612,C712,C713,C722,C723,C732,C733,C752,C801,C802,C803,C806,C808,C811,C812,C821,C822,C823,C831,C832,C841,C842,C852,C853,C864,C865,C866,C867,C881,C882,C891,C892,C893,C901,C902,C903,C904,C905,C906,C907,C908,C909,C910,C911,C912,C913",C0402,C1525
CL05A475MP5NRNC,"C150,C168,C809",C0402,C23733
0402CG270J500NT,"C154,C156",C0402,C1557
CL10A105KB8NNNC,C155,C0603,C15849
CL05A105KA5NQNC,"C159,C807",C0402,C52923
CL10A106KP8NNNC,"C611,C804,C805,C883",C0603,C19702
CL31A226KAHNNNE,"C613,C700,C701,C710,C711,C720,C721,C730,C731,C750,C751",C1206,C12891
GRM32ER61C476KE15L,"C714,C715,C724,C725,C734,C735",C1210,C77101
CL05A474KP5NNNC,"C716,C726,C736",C0402,C47339
CL05C100JB5NNNC,"C717,C727,C737",C0402,C32949
0402CG150J500NT,"C810,C851,C861,C862",C0402,C1548
CL05A225MQ5NSNC,C863,C0402,C12530
CL21A475KAQNNNE,C868,C0805,C1779
SMF15CA,D26,SOD-123FL_L2.8-W1.8-LS3.7-BI,C1509592
KT-0603R,D91,LED-SMD_L1.6-W0.8-R-RD,C2286
KT-0603Y,D92,LED0603-R-RD,C2287
KT-0603G,"D93,D831,D832,D833,D834,D835,D836",LED0603-RD,C12624
SMBJ15A,D750,SMB_L4.6-W3.6-LS5.3-RD,C357961
1N4148W,D841,SOD-123F_L2.7-W1.6-LS3.8-RD,C81598
S1206-S-5.0A,F750,F1206,C553932
S1206-S-3.0A,F751,F1206,C553930
BLM15PX121SN1D,"FB4,FB5,FB601",L0402,C88970
USB4105-GF-A,"J10,J803",TYPE-C-SMD_SBC-160S1A-20-S412,C3020560
KH-SMA-KWE11,"J21,J22,J23,J24,J25,J26",SMA-TH_KH-SMA-KWE11,C7542051
PZ254-2-13-S,J42,HDR-SMD_26P-P2.54-V-M-R2-C13-LS7.5,C3294471
QSFP28 49003-00N011,J602,CONN-SMD_QSFP2849003-00N011,C50159078
PJ-002AH,J750,DC-IN-TH_PJ-002AH,C2961147
HR911130A,J801,RJ45-TH_HR911130A,C54408
TF-01A,J805,TF-SMD_TF-01A,C91145
X2510WV-02-N0SN,J806,CONN-TH_2P-X2510WV-02-N0SN,C843331
MWSA0603S-3R3MT,L701,IND-SMD_L7.0-W6.6,C408446
MWSA0603S-1R5MT,L702,IND-SMD_L7.0-W6.6,C408444
MWSA0603S-2R2MT,L703,IND-SMD_L7.0-W6.6,C408445
SWPA3015S2R2MT,L801,IND-SMD_L3.0-W3.0,C43389
N096-1608TBBIG11-H13,LCD1,OLED-SMD_ST7735S,C2890616
MMBT3904(RANGE:100-300),"Q91,Q92,Q93,Q831,Q832,Q833,Q834,Q835,Q836",SOT-23-3_L2.9-W1.3-P1.90-LS2.4-BR,C20526
AO3400A,"Q841,Q842",SOT-23-3_L2.9-W1.3-P1.90-LS2.4-BR,C20917
0402WGF220JTCE,"R21,R22,R23,R24,R31,R32,R33,R34,R35,R954",R0402,C25092
0402WGF1003TCE,"R25,R26,R513,R713,R740,R750,R752",R0402,C25741
0402WGF1001TCE,"R27,R862,R931,R932,R933,R934,R935,R936",R0402,C11702
0402WGF1002TCE,"R36,R94,R95,R96,R106,R108,R110,R515,R710,R712,R722,R732,R741,R803,R863,R891,R941,R942,R943,R944,R945,R946,R951,R952,R955",R0402,C25744
0402WGF3300TCE,"R91,R92,R93",R0402,C25104
0402WGF1202TCE,"R102,R751",R0402,C25752
0402WGF2201TCE,"R107,R603,R604",R0402,C25879
0402WGF330JTCE,"R121,R122,R123,R124,R811,R812,R821,R822,R831,R832,R841,R842",R0402,C25105
0402WGF8201TCE,"R514,R753",R0402,C25924
0402WGF4701TCE,"R601,R602,R804,R805,R806,R808,R810,R852",R0402,C25900
0402WGF7322TCE,R711,R0402,C26986
0402WGF2202TCE,R714,R0402,C25768
RT0402BRD0720KL,R720,R0402,C705630
RT0402BRD0740K2L,R721,R0402,C852775
RT0402BRD0710KL,R730,R0402,C190095
RT0402BRD0745K3L,R731,R0402,C852795
0402WGF2402TCE,R754,R0402,C25769
0402WGF2702TCE,R755,R0402,C25771
0402WGF2491TCE,R801,R0402,C25884
0402WGF1501TCE,R802,R0402,C25867
0402WGF5100TCE,"R809,R851",R0402,C25123
0402WGF1000TCE,"R813,R814,R823,R824,R833,R834,R843,R844",R0402,C25076
RMC04028.06K1%N,R861,R0402,C325549
0402WGF5101TCE,"R865,R866,R901,R902",R0402,C25905
DSIC04LSGET,SW1,SW-SMD_DSIC04LSGET,C54950
PB-22E86-3.3,SW750,SW-TH_6P-L8.5-W8.5-P2.50-S5.30_PB-22E86,C2848960
TS-1088-AR02016,"SW801,SW802,SW803,SW804",SW-SMD_L3.9-W3.0-P4.45,C720477
RH-5015,"TP702,TP703,TP704",SMD_RH-5015,C5199798
TXU0204PWR,U21,TSSOP-14_L5.0-W4.4-P0.65-LS6.4-BL,C4363888
MCP4922-E/SL,U22,SOIC-14_L8.7-W3.9-P1.27-LS6.0-BL,C39851
NCP730BMT330TBG,U38,WDFN-6_L2.0-W2.0-P0.65-BL-EP-1,C892821
AT93C66B-XHM-B,U39,TSSOP-8_L4.4-W3.0-P0.65-LS6.4-BL,C619884
FT2232HL-REEL,U40,LQFP-64_L10.0-W10.0-P0.50-LS12.0-TL,C27882
SN74AVC2T245RSWR,"U42,U43,U45",WQFN-10_L1.8-W1.4-P0.40-BL,C128418
USBLC6-2P6,U60,SOT-563_L1.6-W1.2-P0.50-LS1.6-BL,C21713974
MS90C031,"U81,U82,U83,U84",SOP-16_L10.0-W3.9-P1.27-LS6.0-BL,C1508988
MS90C032,"U91,U92,U93,U94",SOP-16_L10.0-W3.9-P1.27-LS6.0-BL,C1508989
SN74LVC1G07DCKR,U511,SC-70-5_L2.1-W1.3-P0.65-LS2.1-BR,C7830
TPS56528DDAR,"U701,U702,U703",SOIC-8_L4.9-W3.9-P1.27-LS6.0-BL-EP,C138716
TPS2121RUXR,U750,VQFN-HR-12_L2.5-W2.0-P0.50-BL,C485916
RTL8211F-CG,U801,WQFN-40_L5.0-W5.0-P0.4-BL-EP,C187932
USB3320C-EZK-TR,U802,QFN-32_L5.0-W5.0-P0.50-BL-EP3.4,C132156
TXS0108EPWR,U806,TSSOP-20_L6.5-W4.4-P0.65-LS6.4-BL,C17206
SN74LV4T125RGYR,U807,VQFN-14_L3.5-W3.5-P0.50-BL-EP,C411879
OB3225125MLDB6SI-00,X901,OSC-SMD_6P-L3.2-W2.5-BL_SG3225EAN,C5173622
ABM8G-12.000MHZ-18-D2Y-T,Y7,CRYSTAL-SMD_4P-L3.2-W2.5-BL,C596904
OB3225156.25MLDB6SI-00,Y601,OSC-SMD_6P-L3.2-W2.5-BL,C5210644
X322525MOB4SI,Y801,CRYSTAL-SMD_4P-L3.2-W2.5-BL,C9006
X322512MOB4SI,Y802,CRYSTAL-SMD_4P-L3.2-W2.5-BL,C70565
